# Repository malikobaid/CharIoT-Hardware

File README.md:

# CharIoT Custom Sensor PCB
Can be ordered from dirtypcb http://dirtypcbs.com/rendering/details/fk5t/ESP12E_DHT22_NO_RF_NEW_v1.zip

A DHT22 and ESP8266-12F based wifi temperature and humidity sensor that records and sends data to a custom influxdb server.

## Copyright and License

Copyright 2016-2017 CharIoT. <br> Released under the [MIT](https://github.com/BlackrockDigital/startbootstrap-landing-page/blob/gh-pages/LICENSE) license.

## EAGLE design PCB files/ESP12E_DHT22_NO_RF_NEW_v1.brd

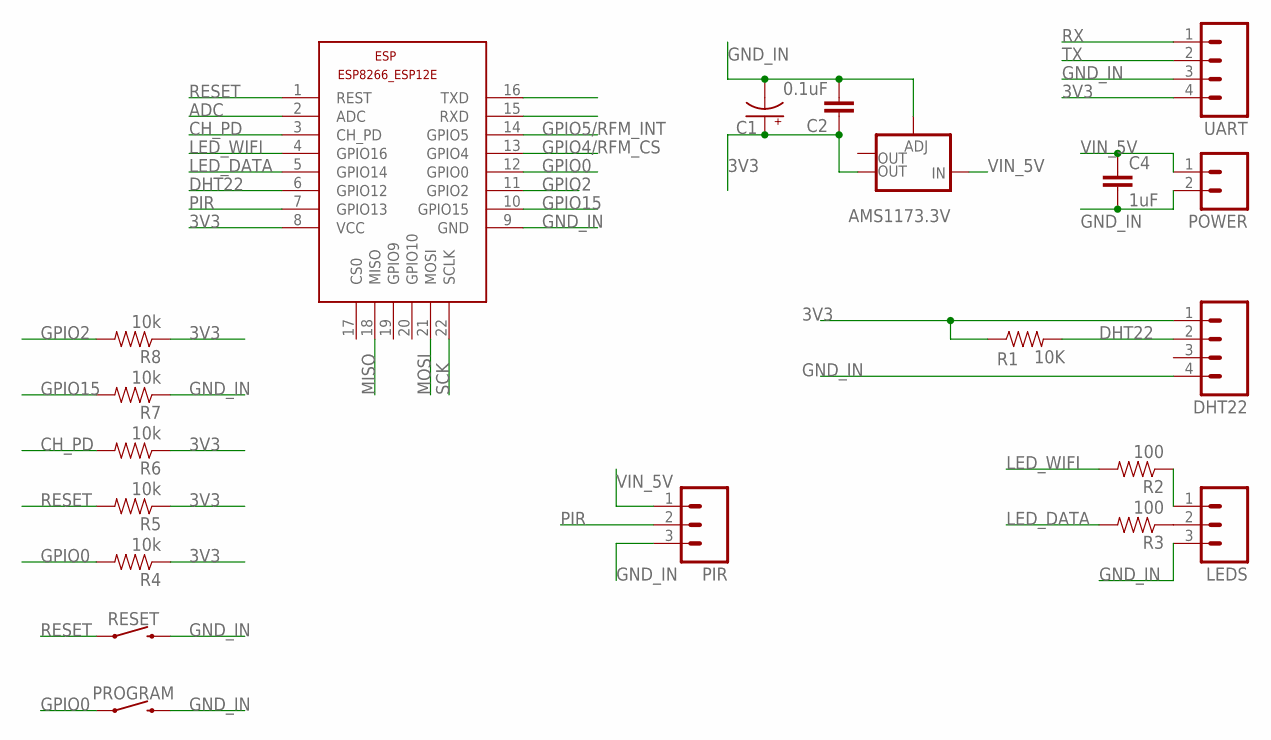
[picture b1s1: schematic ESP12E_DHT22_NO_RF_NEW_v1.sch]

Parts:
AMS1173.3V: V_REG_LM1117SOT223; SOT223
C1: CAP_POLC; PANASONIC_C
C2: 0.1uF; 0603-CAP
C4: 1uF; 0603-CAP
DHT22: M04LONGPADS; 1X04_LONGPADS
ESP: ESP8266-12EESP8266-ESP12E; ESP8266-ESP12E
LEDS: M03PTH; 1X03
PIR: M03PTH; 1X03
POWER: M02PTH; 1X02
PROGRAM: MOMENTARY-SWITCH-SPST-PTH-6.0MM-KIT; TACTILE_SWITCH_PTH_6.0MM_KIT
R1: 10K; 0603-RES
R2, R3: 100; 0603-RES
R4, R5, R6, R7, R8: 10k; 0603-RES
RESET: MOMENTARY-SWITCH-SPST-PTH-6.0MM-KIT; TACTILE_SWITCH_PTH_6.0MM_KIT
UART: M04LONGPADS; 1X04_LONGPADS

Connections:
3V3: AMS1173.3V.2 (OUT), C1.+, C2.1, DHT22.1, ESP.8 (VCC), R1.1, R4.1, R5.1, R6.1, R8.1, UART.4
ADC: ESP.2 (ADC)
CH_PD: ESP.3 (CH_PD), R6.2
DHT22: DHT22.2, ESP.6 (GPIO12), R1.2
GND_IN: AMS1173.3V.1 (ADJ), C1.-, C2.2, C4.2, DHT22.4, ESP.9 (GND), LEDS.3, PIR.3, POWER.2, PROGRAM.3 (2), R7.1, RESET.3 (2), UART.3
GPIO0: ESP.12 (GPIO0), PROGRAM.1, R4.2
GPIO2: ESP.11 (GPIO2), R8.2
GPIO4/RFM_CS: ESP.13 (GPIO4)
GPIO5/RFM_INT: ESP.14 (GPIO5)
GPIO15: ESP.10 (GPIO15), R7.2
LED_DATA: ESP.5 (GPIO14), R3.2
LED_WIFI: ESP.4 (GPIO16), R2.2
MISO: ESP.18 (MISO)
MOSI: ESP.21 (MOSI)
unnamed: LEDS.2, R3.1
unnamed: LEDS.1, R2.1
PIR: ESP.7 (GPIO13), PIR.2
RESET: ESP.1 (REST), R5.2, RESET.1
RX: ESP.16 (TXD), UART.1
SCK: ESP.22 (SCLK)
TX: ESP.15 (RXD), UART.2
VIN_5V: AMS1173.3V.3 (IN), C4.1, PIR.1, POWER.1

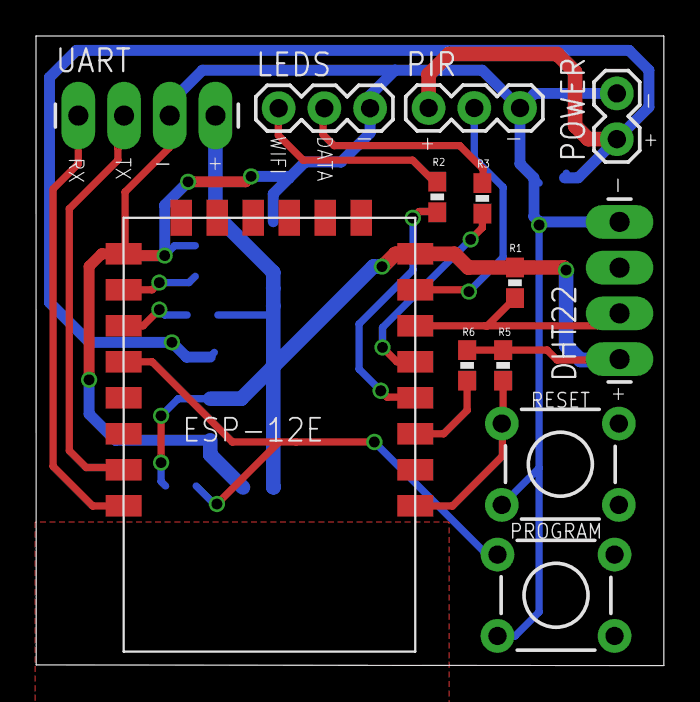
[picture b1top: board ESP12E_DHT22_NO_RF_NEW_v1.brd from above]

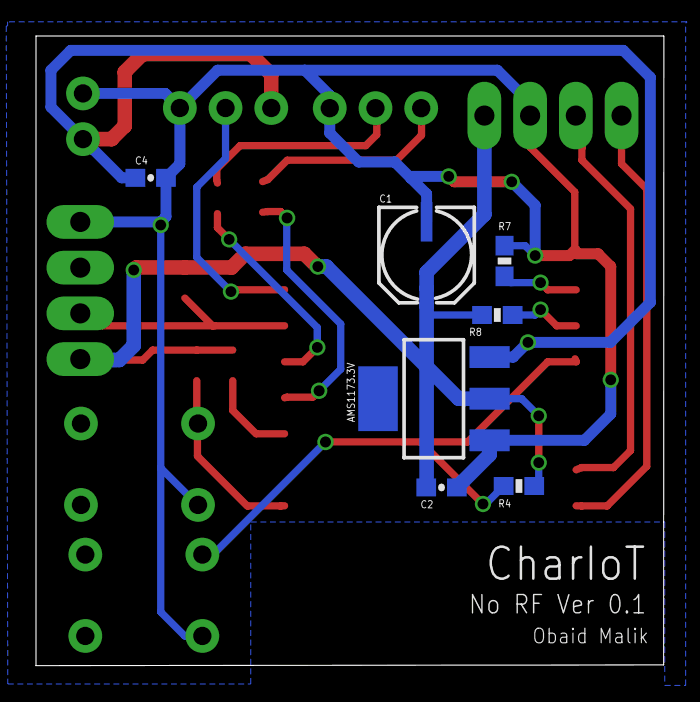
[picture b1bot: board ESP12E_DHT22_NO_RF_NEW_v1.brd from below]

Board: 2 copper layers, 34.9 x 35.0 mm, 20 parts (7 on the bottom side), 16 nets.

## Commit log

2017-10-05 Sensor Code

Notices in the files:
parts and their libraries:
SparkFun-PowerIC: Licensing: Creative Commons ShareAlike 4.0 International - https://creativecommons.org/licenses/by-sa/4.0
